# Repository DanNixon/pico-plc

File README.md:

# Pico-PLC

A [Raspberry Pi Pico](https://www.raspberrypi.com/products/raspberry-pi-pico/) powered PLC like general purpose control board.

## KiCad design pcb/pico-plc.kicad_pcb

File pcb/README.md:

# Pico-PLC PCB

[KiCad](https://www.kicad.org/) flavoured design files for the Pico-PLC PCB.

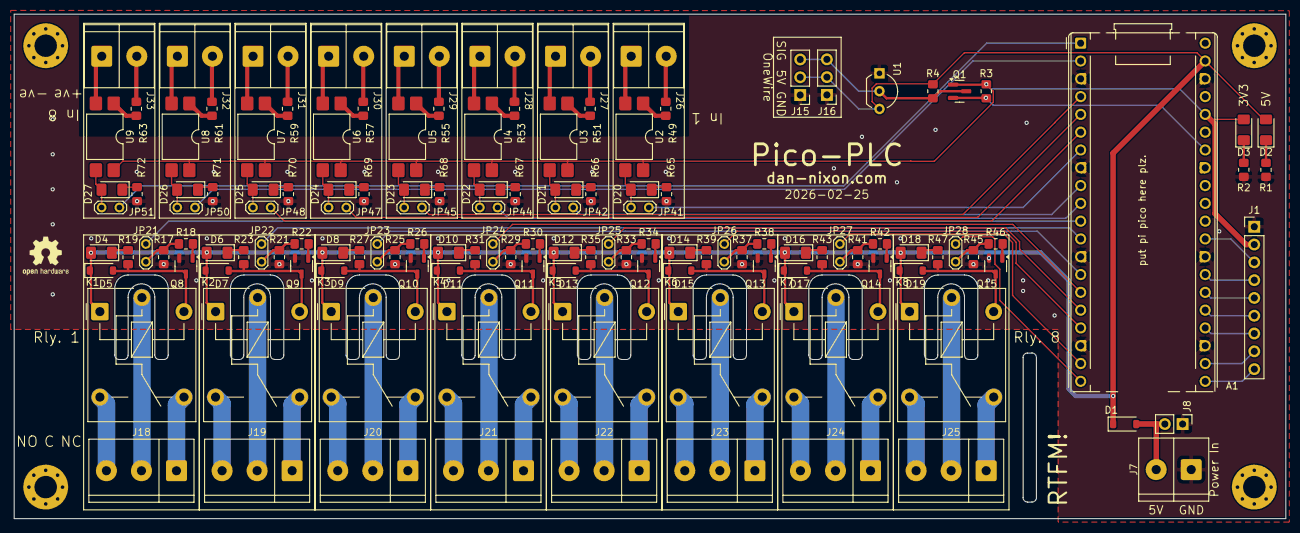
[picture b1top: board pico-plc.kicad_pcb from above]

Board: 2 copper layers, 181.5 x 72.0 mm, 139 parts (0 on the bottom side), 127 nets.

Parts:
A1: RaspberryPi_Pico; RaspberryPi_Pico_Common_THT
D1, D5, D7, D9, D11, D13, D15, D17, D19: D_Schottky; D_SOD-123
D2: Power In LED; LED_1206_3216Metric_Pad1.42x1.75mm_HandSolder
D3: 3.3v On LED; LED_1206_3216Metric_Pad1.42x1.75mm_HandSolder
D4, D6, D8, D10, D12, D14, D16, D18, D20, D21, D22, D23, D24, D25, D26, D27: LED; LED_1206_3216Metric_Pad1.42x1.75mm_HandSolder
H1, H2, H3, H4: MountingHole; MountingHole_3.2mm_M3_Pad_Via
J1: Conn_01x09; PinHeader_1x09_P2.54mm_Vertical
J7, J26, J27, J28, J29, J30, J31, J32, J33: Screw_Terminal_01x02; CTB7000-2
J8: Conn_01x02; PinHeader_1x02_P2.54mm_Vertical
J15, J16: Conn_01x03; PinHeader_1x03_P2.54mm_Vertical
J18, J19, J20, J21, J22, J23, J24, J25: Screw_Terminal_01x03; CTB7000-3
JP21, JP22, JP23, JP24, JP25, JP26, JP27, JP28, JP41, JP42, JP44, JP45, JP47, JP48, JP50, JP51: Jumper_2_Open; TestPoint_2Pads_Pitch2.54mm_Drill0.8mm
K1, K2, K3, K4, K5, K6, K7, K8: Relay_SPDT; Relay_SPDT_Finder_36.11
Q1: BSS138; SOT-23
Q8, Q9, Q10, Q11, Q12, Q13, Q14, Q15: NDS355AN; SOT-23-3
R1, R18, R19, R22, R23, R26, R27, R30, R31, R34, R35, R38, R39, R42, R43, R46, R47, R65, R66, R67, R68, R69, R70, R71, R72: 470; R_0805_2012Metric_Pad1.20x1.40mm_HandSolder
R2: 330; R_0805_2012Metric_Pad1.20x1.40mm_HandSolder
R3, R4: 2.2K; R_0805_2012Metric_Pad1.20x1.40mm_HandSolder
R17, R21, R25, R29, R33, R37, R41, R45: 10k; R_0805_2012Metric_Pad1.20x1.40mm_HandSolder
R49, R51, R53, R55, R57, R59, R61, R63: 4k7; R_0805_2012Metric_Pad1.20x1.40mm_HandSolder
U1: DS18B20; TO-92_Inline_Wide
U2, U3, U4, U5, U6, U7, U8, U9: VO615A; SMDIP-4_W9.53mm

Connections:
+3V3: A1.36 (3V3), D3.2 (A), J1.2, Q1.1 (G), R3.1, U2.4, U3.4, U4.4, U5.4, U6.4, U7.4, U8.4, U9.4
+5V: A1.39 (VSYS), D1.1 (K), D2.2 (A), D4.2 (A), D5.1 (K), D6.2 (A), D7.1 (K), D8.2 (A), D9.1 (K), D10.2 (A), D11.1 (K), D12.2 (A), D13.1 (K), D14.2 (A), D15.1 (K), D16.2 (A), D17.1 (K), D18.2 (A), D19.1 (K), J15.2, J16.2, K1.A1, K2.A1, K3.A1, K4.A1, K5.A1, K6.A1, K7.A1, K8.A1, R4.1, U1.3 (V_{DD})
/IO0: A1.1 (GPIO0), JP51.2 (B)
/IO1: A1.2 (GPIO1), JP50.2 (B)
/IO2: A1.4 (GPIO2), JP45.2 (B)
/IO3: A1.5 (GPIO3), JP47.2 (B)
/IO4: A1.6 (GPIO4), JP48.2 (B)
/IO5: A1.7 (GPIO5), JP41.2 (B)
/IO6: A1.9 (GPIO6), JP42.2 (B)
/IO7: A1.10 (GPIO7), JP44.2 (B)
/IO8: A1.11 (GPIO8), JP21.1 (A)
/IO9: A1.12 (GPIO9), JP22.1 (A)
/IO10: A1.14 (GPIO10), JP23.1 (A)
/IO11: A1.15 (GPIO11), JP24.1 (A)
/IO12: A1.16 (GPIO12), JP25.1 (A)
/IO13: A1.17 (GPIO13), JP26.1 (A)
/IO14: A1.19 (GPIO14), JP27.1 (A)
/IO15: A1.20 (GPIO15), JP28.1 (A)
/IO16: A1.21 (GPIO16), J1.9
/IO17: A1.22 (GPIO17), J1.8
/IO18: A1.24 (GPIO18), J1.7
/IO19: A1.25 (GPIO19), J1.6
/IO20: A1.26 (GPIO20), J1.5
/IO21: A1.27 (GPIO21), J1.4
/IO22: A1.29 (GPIO22), J1.3
/IO28: A1.34 (GPIO28_ADC2), Q1.2 (S), R3.2
/OneWire/ONEWIRE_5V: J15.3, J16.3, Q1.3 (D), R4.2, U1.2 (DQ)
/Opto Inputs/Input 0/COM: J26.1, U2.2
/Opto Inputs/Input 0/SIG: J26.2, R49.1
/Opto Inputs/Input 1/COM: J27.1, U3.2
/Opto Inputs/Input 1/SIG: J27.2, R51.1
/Opto Inputs/Input 2/COM: J28.1, U4.2
/Opto Inputs/Input 2/SIG: J28.2, R53.1
/Opto Inputs/Input 3/COM: J29.1, U5.2
/Opto Inputs/Input 3/SIG: J29.2, R55.1
/Opto Inputs/Input 4/COM: J30.1, U6.2
/Opto Inputs/Input 4/SIG: J30.2, R57.1
/Opto Inputs/Input 5/COM: J31.1, U7.2
/Opto Inputs/Input 5/SIG: J31.2, R59.1
/Opto Inputs/Input 6/COM: J32.1, U8.2
/Opto Inputs/Input 6/SIG: J32.2, R61.1
/Opto Inputs/Input 7/COM: J33.1, U9.2
/Opto Inputs/Input 7/SIG: J33.2, R63.1
/Power/Power In: D1.2 (A), J7.2, J8.2
/Relays/Relay 0/COM: J18.2, K1.11
/Relays/Relay 0/NC: J18.1, K1.12
/Relays/Relay 0/NO: J18.3, K1.14
/Relays/Relay 1/COM: J19.2, K2.11
/Relays/Relay 1/NC: J19.1, K2.12
/Relays/Relay 1/NO: J19.3, K2.14
/Relays/Relay 2/COM: J20.2, K3.11
/Relays/Relay 2/NC: J20.1, K3.12
/Relays/Relay 2/NO: J20.3, K3.14
/Relays/Relay 3/COM: J21.2, K4.11
/Relays/Relay 3/NC: J21.1, K4.12
/Relays/Relay 3/NO: J21.3, K4.14
/Relays/Relay 4/COM: J22.2, K5.11
/Relays/Relay 4/NC: J22.1, K5.12
/Relays/Relay 4/NO: J22.3, K5.14
/Relays/Relay 5/COM: J23.2, K6.11
/Relays/Relay 5/NC: J23.1, K6.12
/Relays/Relay 5/NO: J23.3, K6.14
/Relays/Relay 6/COM: J24.2, K7.11
/Relays/Relay 6/NC: J24.1, K7.12
/Relays/Relay 6/NO: J24.3, K7.14
/Relays/Relay 7/COM: J25.2, K8.11
/Relays/Relay 7/NC: J25.1, K8.12
/Relays/Relay 7/NO: J25.3, K8.14
GND: A1.3 (GND), A1.8 (GND), A1.13 (GND), A1.18 (GND), A1.23 (GND), A1.28 (GND), A1.38 (GND), J1.1, J7.1, J8.1, J15.1, J16.1, Q8.2 (S), Q9.2 (S), Q10.2 (S), Q11.2 (S), Q12.2 (S), Q13.2 (S), Q14.2 (S), Q15.2 (S), R1.2, R2.2, R17.2, R21.2, R25.2, R29.2, R33.2, R37.2, R41.2, R45.2, R65.2, R66.2, R67.2, R68.2, R69.2, R70.2, R71.2, R72.2, U1.1 (GND)
unnamed: D2.1 (K), R1.1
unnamed: D3.1 (K), R2.1
unnamed: D4.1 (K), R19.1
unnamed: D5.2 (A), K1.A2, Q8.3 (D), R19.2
unnamed: D6.1 (K), R23.1
unnamed: D7.2 (A), K2.A2, Q9.3 (D), R23.2
unnamed: D8.1 (K), R27.1
unnamed: D9.2 (A), K3.A2, Q10.3 (D), R27.2
unnamed: D10.1 (K), R31.1
unnamed: D11.2 (A), K4.A2, Q11.3 (D), R31.2
unnamed: D12.1 (K), R35.1
unnamed: D13.2 (A), K5.A2, Q12.3 (D), R35.2
unnamed: D14.1 (K), R39.1
unnamed: D15.2 (A), K6.A2, Q13.3 (D), R39.2
unnamed: D16.1 (K), R43.1
unnamed: D17.2 (A), K7.A2, Q14.3 (D), R43.2
unnamed: D18.1 (K), R47.1
unnamed: D19.2 (A), K8.A2, Q15.3 (D), R47.2
unnamed: D20.2 (A), JP41.1 (A), U2.3
unnamed: D20.1 (K), R65.1
unnamed: D21.2 (A), JP42.1 (A), U3.3
unnamed: D21.1 (K), R66.1
unnamed: D22.2 (A), JP44.1 (A), U4.3
unnamed: D22.1 (K), R67.1
unnamed: D23.2 (A), JP45.1 (A), U5.3
unnamed: D23.1 (K), R68.1
unnamed: D24.2 (A), JP47.1 (A), U6.3
unnamed: D24.1 (K), R69.1
unnamed: D25.2 (A), JP48.1 (A), U7.3
unnamed: D25.1 (K), R70.1
unnamed: D26.2 (A), JP50.1 (A), U8.3
unnamed: D26.1 (K), R71.1
unnamed: D27.2 (A), JP51.1 (A), U9.3
unnamed: D27.1 (K), R72.1
unnamed: JP21.2 (B), R17.1, R18.1
unnamed: JP22.2 (B), R21.1, R22.1
unnamed: JP23.2 (B), R25.1, R26.1
unnamed: JP24.2 (B), R29.1, R30.1
unnamed: JP25.2 (B), R33.1, R34.1
unnamed: JP26.2 (B), R37.1, R38.1
unnamed: JP27.2 (B), R41.1, R42.1
unnamed: JP28.2 (B), R45.1, R46.1
unnamed: Q8.1 (G), R18.2
unnamed: Q9.1 (G), R22.2
unnamed: Q10.1 (G), R26.2
unnamed: Q11.1 (G), R30.2
unnamed: Q12.1 (G), R34.2
unnamed: Q13.1 (G), R38.2
unnamed: Q14.1 (G), R42.2
unnamed: Q15.1 (G), R46.2
unnamed: R49.2, U2.1
unnamed: R51.2, U3.1
unnamed: R53.2, U4.1
unnamed: R55.2, U5.1
unnamed: R57.2, U6.1
unnamed: R59.2, U7.1
unnamed: R61.2, U8.1
unnamed: R63.2, U9.1

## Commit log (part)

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2024-10-21 Bump embassy-executor in /demo-firmware in the cargo-dependencies group
    Bumps the cargo-dependencies group in /demo-firmware with 1 update: [embassy-executor](https://github.com/embassy-rs/embassy).
    Updates `embassy-executor` from 0.6.0 to 0.6.1
    - [Commits](https://github.com/embassy-rs/embassy/compare/embassy-executor-v0.6.0...embassy-executor-v0.6.1)
    ---
    updated-dependencies:
    - dependency-name: embassy-executor
2024-12-01 Bump DeterminateSystems/nix-installer-action from 14 to 16
    Bumps [DeterminateSystems/nix-installer-action](https://github.com/determinatesystems/nix-installer-action) from 14 to 16.
    - [Release notes](https://github.com/determinatesystems/nix-installer-action/releases)
    - [Commits](https://github.com/determinatesystems/nix-installer-action/compare/v14...v16)
    ---
    updated-dependencies:
    - dependency-name: DeterminateSystems/nix-installer-action
2024-12-01 Bump the cargo-dependencies group in /demo-firmware with 5 updates
    Bumps the cargo-dependencies group in /demo-firmware with 5 updates:
    | Package | From | To |
    | --- | --- | --- |
    | [cortex-m-rt](https://github.com/rust-embedded/cortex-m) | `0.7.3` | `0.7.5` |
    | [embassy-executor](https://github.com/embassy-rs/embassy) | `0.6.1` | `0.6.3` |
    | [defmt](https://github.com/knurling-rs/defmt) | `0.3.8` | `0.3.10` |
2024-12-15 Flake update
2025-02-01 Bump embassy-sync in /demo-firmware in the cargo-dependencies group
    Bumps the cargo-dependencies group in /demo-firmware with 1 update: [embassy-sync](https://github.com/embassy-rs/embassy).
    Updates `embassy-sync` from 0.6.1 to 0.6.2
    - [Commits](https://github.com/embassy-rs/embassy/commits)
    ---
    updated-dependencies:
    - dependency-name: embassy-sync
2025-02-12 Switch to devenv
2025-02-12 cargo update
2025-02-12 update embassy libs and rust version
2025-02-17 fixup! update embassy libs and rust version
2025-02-23 Convert PCB to KiCad 9.0 format
2025-02-28 Use larger screw terminals, adjust layout to suit
2025-03-01 Convert PCB to KiCad 9 project
2025-03-01 Rerun DRC after KiCad 9 conversion
2025-03-01 Update component properties and rerun ERC
2025-03-04 pcb: disconnect mounting holes from GND, fix dimension annotations
2025-03-13 Add board support package/crate
    - Adds board support crate (heavily inspired by https://github.com/lulf/microbit-bsp)
    - Move demo firmware to an example
2025-03-13 Add ability to steal peripherals to BSP
    Required for panic handlers.
2025-03-15 Tidy firmware example
2025-03-17 Add case
2025-04-01 Bump cachix/cachix-action from 15 to 16
    Bumps [cachix/cachix-action](https://github.com/cachix/cachix-action) from 15 to 16.
    - [Release notes](https://github.com/cachix/cachix-action/releases)
    - [Commits](https://github.com/cachix/cachix-action/compare/v15...v16)
    ---
    updated-dependencies:
    - dependency-name: cachix/cachix-action
2025-04-01 Bump cachix/install-nix-action from 30 to 31
    Bumps [cachix/install-nix-action](https://github.com/cachix/install-nix-action) from 30 to 31.
    - [Release notes](https://github.com/cachix/install-nix-action/releases)
    - [Commits](https://github.com/cachix/install-nix-action/compare/v30...v31)
    ---
    updated-dependencies:
    - dependency-name: cachix/install-nix-action
2025-04-09 bsp: pico 2 support
2025-04-28 bsp: set targets in rust-toolchain.toml
2025-04-28 bsp: use latest Rust version
2025-04-28 bsp: remove unnecessary gitignore files
2025-04-28 devenv: update
2025-07-03 Fix dependabot cargo config
2025-07-03 build(deps): bump the cargo-dependencies group
    Updates the requirements on [defmt](https://github.com/knurling-rs/defmt) and [defmt-rtt](https://github.com/knurling-rs/defmt) to permit the latest version.
    Updates `defmt` to 1.0.1
    - [Release notes](https://github.com/knurling-rs/defmt/releases)
    - [Changelog](https://github.com/knurling-rs/defmt/blob/main/CHANGELOG.md)
    - [Commits](https://github.com/knurling-rs/defmt/compare/defmt-v0.3.10...defmt-v1.0.1)
    Updates `defmt-rtt` to 1.0.0
2025-07-03 build(deps): bump the cargo-dependencies group
    Updates the requirements on [assign-resources](https://github.com/adamgreig/assign-resources), [defmt](https://github.com/knurling-rs/defmt), [defmt-rtt](https://github.com/knurling-rs/defmt) and [pa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
    Updates `assign-resources` to 0.5.0
    - [Changelog](https://github.com/adamgreig/assign-resources/blob/main/CHANGELOG.md)
    - [Commits](https://github.com/adamgreig/assign-resources/compare/v0.4.1...v0.5.0)
    Updates `defmt` to 1.0.1
    - [Release notes](https://github.com/knurling-rs/defmt/releases)
2025-07-03 build(deps): bump the cargo-dependencies group across 1 directory with 3 updates
    Updates the requirements on [defmt](https://github.com/knurling-rs/defmt), [defmt-rtt](https://github.com/knurling-rs/defmt) and [panic-probe](https://github.com/knurling-rs/defmt) to permit the late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
    Updates `defmt` to 1.0.1
    - [Release notes](https://github.com/knurling-rs/defmt/releases)
    - [Changelog](https://github.com/knurling-rs/defmt/blob/main/CHANGELOG.md)
    - [Commits](https://github.com/knurling-rs/defmt/compare/defmt-v0.3.10...defmt-v1.0.1)
    Updates `defmt-rtt` to 1.0.0
2025-07-03 build(deps): bump the cargo-dependencies group across 1 directory with 3 updates
    ---
    updated-dependencies:
    - dependency-name: defmt
    dependency-version: 1.0.1
    dependency-type: direct:production
    dependency-group: cargo-dependencies
2025-07-23 Devenv update
2025-07-23 Use probe-rs from stable
2025-07-23 Update Rust version and edition
2025-07-23 Update Cargo dependencies
2025-08-01 build(deps): update embassy-executor requirement
    Updates the requirements on [embassy-executor](https://github.com/embassy-rs/embassy) to permit the latest version.
    Updates `embassy-executor` to 0.7.0
    - [Changelog](https://github.com/embassy-rs/embassy/blob/main/RELEASE.md)
    - [Commits](https://github.com/embassy-rs/embassy/compare/embassy-executor-v0.7.0...embassy-executor-v0.7.0)
    ---
    updated-dependencies:
2025-08-04 Update Rust version
2025-09-02 build(deps): bump the cargo-dependencies group
    Updates the requirements on [embassy-executor](https://github.com/embassy-rs/embassy) and [embassy-time](https://github.com/embassy-rs/embassy) to permit the latest version.
    Updates `embassy-executor` to 0.9.1
    - [Changelog](https://github.com/embassy-rs/embassy/blob/main/RELEASE.md)
    - [Commits](https://github.com/embassy-rs/embassy/compare/embassy-executor-v0.8.0...embassy-executor-v0.9.1)
    Updates `embassy-time` to 0.5.0
    - [Changelog](https://github.com/embassy-rs/embassy/blob/main/RELEASE.md)
2025-09-02 build(deps): update embassy-rp requirement
    Updates the requirements on [embassy-rp](https://github.com/embassy-rs/embassy) to permit the latest version.
    Updates `embassy-rp` to 0.8.0
    - [Changelog](https://github.com/embassy-rs/embassy/blob/main/RELEASE.md)
    - [Commits](https://github.com/embassy-rs/embassy/compare/embassy-rp-v0.7.0...embassy-rp-v0.8.0)
    ---
    updated-dependencies:
2025-09-02 build(deps): bump actions/checkout from 4 to 5
    Bumps [actions/checkout](https://github.com/actions/checkout) from 4 to 5.
    - [Release notes](https://github.com/actions/checkout/releases)
    - [Changelog](https://github.com/actions/checkout/blob/main/CHANGELOG.md)
    - [Commits](https://github.com/actions/checkout/compare/v4...v5)
    ---
    updated-dependencies:
2025-12-01 Update devenv inputs
2025-12-01 build(deps): bump actions/checkout from 5 to 6
    Bumps [actions/checkout](https://github.com/actions/checkout) from 5 to 6.
    - [Release notes](https://github.com/actions/checkout/releases)
    - [Changelog](https://github.com/actions/checkout/blob/main/CHANGELOG.md)
    - [Commits](https://github.com/actions/checkout/compare/v5...v6)
    ---
    updated-dependencies:
2026-01-16 Switch to Nix flake, add typos
2026-02-14 Remove BSP
    Was sufficiently simple to not be worth maintaining.
2026-02-14 Add pins to readme
2026-02-26 Simpler bottom mount case
2026-03-20 New board revision
2026-04-02 build(deps): bump DeterminateSystems/nix-installer-action from 21 to 22
    Bumps [DeterminateSystems/nix-installer-action](https://github.com/determinatesystems/nix-installer-action) from 21 to 22.
    - [Release notes](https://github.com/determinatesystems/nix-installer-action/releases)
    - [Commits](https://github.com/determinatesystems/nix-installer-action/compare/v21...v22)
    ---
    updated-dependencies:
    - dependency-name: DeterminateSystems/nix-installer-action
2026-05-03 Add .history to gitignore
